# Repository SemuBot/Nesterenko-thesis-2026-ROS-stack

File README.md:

# ROS 2 Stack for Social Humanoid Robot SemuBot

## Project Overview
This repository provides a modular ROS 2 stack architecture for **SemuBot**, an open-source social humanoid robot developed at the University of Tartu.

## Thesis Context
Previous SemuBot thesis works developed separate subsystems (face/neck, audio, speech, vision, power, arms, servo control, and initial ROS 2 integration).  
This repository organizes those efforts into a unified ROS 2 stack with clearer package boundaries and safer integration flow.

## Repository Purpose
The repository is intended to provide a maintainable, buildable, and testable architecture for future students and researchers extending SemuBot.

## Architecture Overview
Main architecture layers:
- robot description
- hardware abstraction
- control
- perception
- interaction/behavior
- navigation
- manipulation
- simulation/visualization
- system monitoring

## Robot Description and Mesh Strategy
- The active `semubot_description` now uses **actual SemuBot visual meshes** for RViz visualization.
- Collision geometry remains **simplified** (cylinders/boxes/spheres) for navigation and simulation stability.
- Nav2 behavior depends primarily on TF, odometry, `/cmd_vel`, `/scan`, and footprint/costmap parameters.
- The decorative visual mesh model is intentionally different from the navigation collision model.

## Package Structure
Primary stack lives in `semubot_ros2_ws/src/`:

- `semubot_description`
- `semubot_bringup`
- `semubot_control`
- `semubot_hardware`
- `semubot_interfaces`
- `semubot_behavior`
- `semubot_audio`
- `semubot_vision`
- `semubot_speech`
- `semubot_face`
- `semubot_arm`
- `semubot_navigation`
- `semubot_moveit_config`
- `semubot_simulation`
- `semubot_system_monitor`
- `semubot_test_tools`

## Requirements
- Ubuntu 24.04 (recommended)
- ROS 2 Jazzy (recommended target)
- Note: some legacy subsystem code was originally developed for ROS 2 Humble. Keep compatibility notes when reusing older components.

## Installation
```bash
cd semubot_ros2_ws
rosdep install --from-paths src --ignore-src -r -y
```

## Build Instructions
```bash
cd semubot_ros2_ws
rosdep install --from-paths src --ignore-src -r -y
colcon build
source install/setup.bash
```

## Launch Instructions
```bash
ros2 launch semubot_bringup visualization.launch.py
ros2 launch semubot_bringup mock_robot.launch.py
ros2 launch semubot_bringup navigation_readiness.launch.py
ros2 launch semubot_bringup demo_behavior.launch.py
```

## Mock Nav2 Integration
Use mock Nav2 mode to validate architecture readiness without controlling the real robot:

```bash
ros2 launch semubot_bringup nav2_mock.launch.py
```

This mode is safe by default and routes `/cmd_vel` through mock/safe nodes only.
See: `semubot_ros2_ws/docs/nav2_mock_integration.md`.

## Basic Testing Commands
```bash
ros2 node list
ros2 topic list
ros2 topic echo /joint_states
ros2 topic echo /odom
ros2 topic echo /semubot/demo_state
ros2 topic pub /cmd_vel geometry_msgs/msg/Twist "{linear: {x: 0.05, y: 0.0, z: 0.0}, angular: {x: 0.0, y: 0.0, z: 0.05}}"
```

## Safe `/cmd_vel` Test
`semubot_hardware/safe_cmd_vel_receiver_node` validates velocity limits and rejects unsafe commands before any real hardware forwarding.

`semubot_hardware/mock_base_hardware_node` is used for navigation readiness: it consumes `/cmd_vel`, publishes mock `/odom`, and broadcasts dynamic `odom -> base_link` TF.

Default safety parameters:
- `max_linear_velocity = 0.10`
- `max_angular_velocity = 0.30`
- `enable_real_motion = false`

## Real Robot Safety Warning
Real robot motion is disabled by default and must only be tested under supervised lab conditions with:
- low velocity limits,
- emergency power access,
- sufficient free space,
- one nearby safety observer.

See full protocol: `semubot_ros2_ws/docs/lab_test_protocol.md`.

## Documentation Links
- Getting started: `semubot_ros2_ws/docs/getting_started.md`
- Architecture: `semubot_ros2_ws/docs/architecture.md`
- Navigation readiness: `semubot_ros2_ws/docs/navigation_readiness.md`
- Testing plan: `semubot_ros2_ws/docs/testing_plan.md`
- Lab safety protocol: `semubot_ros2_ws/docs/lab_test_protocol.md`
- Previous subsystem context: `semubot_ros2_ws/docs/previous_work.md`
- Demos and media index: `semubot_ros2_ws/docs/demos.md`
- Future roadmap: `semubot_ros2_ws/docs/future_work.md`
- Media policy: `semubot_ros2_ws/media/README.md`

## Future Work
Near-term priorities:
- validate real odometry sources and obstacle sensing for Nav2,
- integrate validated hardware drivers behind safety wrappers,
- migrate mock nodes to production subsystem integrations,
- stage Nav2 and MoveIt 2 onboarding,
- expand automated test and CI coverage.

## Contribution Guidelines for Future Students
1. Keep package responsibilities clear and documented.
2. Prefer standard ROS 2 messages unless custom interfaces are necessary.
3. Keep real motion disabled by default in new code paths.
4. Add launch and test instructions with every subsystem change.
5. Place large media in `semubot_ros2_ws/media/` and reference it from `docs/demos.md` (do not overload this root README).

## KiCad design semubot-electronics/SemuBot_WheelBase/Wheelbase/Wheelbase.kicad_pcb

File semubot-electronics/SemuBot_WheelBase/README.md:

# Wheelbase

## Overview

This project implements a BLDC motor control wheelbase using an STM32 microcontroller, 3-phase gate drivers, and high-precision current sensing.

---

## Components

### Microcontroller
* **STM32F303RET6**

### BLDC Driver
* **DRV8353FSRTAR**
  3-phase gate driver for MOSFET control.

### Current Sensing
* **ADS131M03IRUKT**
  3-channel, 24-bit, simultaneous-sampling Delta-Sigma ADC for current measurement.

### MOSFETs
* **AON7262E**
  N-channel MOSFETs for power stage switching.

### Voltage Regulation
* **RT9013-33GB**
  3.3V LDO regulator.

### Power Input & Connectors
* **XT30PW-M**
  Main DC power input connector.

* **MR30PW-M**
  Motor phase power connection.

* **10155435-00011LF (Amphenol)**
  USB Type-C connector.

* **B5B-XH-A_LF__SN_ (JST XH)**
  5-pin connector for peripherals (e.g., Hall/Sensor inputs).

* **DS1013-10SSIB1**
  General purpose I/O connector.

### ESD Protection
* **PRTR5V0U2X**
  ESD protection for data lines.

### Timing & Clock
* **ECS-2520MVLC-081.92-CN-TR**
  8.192 MHz Oscillator.
* **X322516MLB4SI**
  Secondary oscillator for system timing.

### User Interface
* **SWT0211-050010GSA_REVA**
  Tactile switch for system reset or user input.

---

## Technical Summary

### Power Stage
* **MOSFETs:** 18x AON7262E
* **Gate Drivers:** 3x DRV8353FSRTAR
* **Current Sense Resistors:** 9x 10mΩ (2512 package)

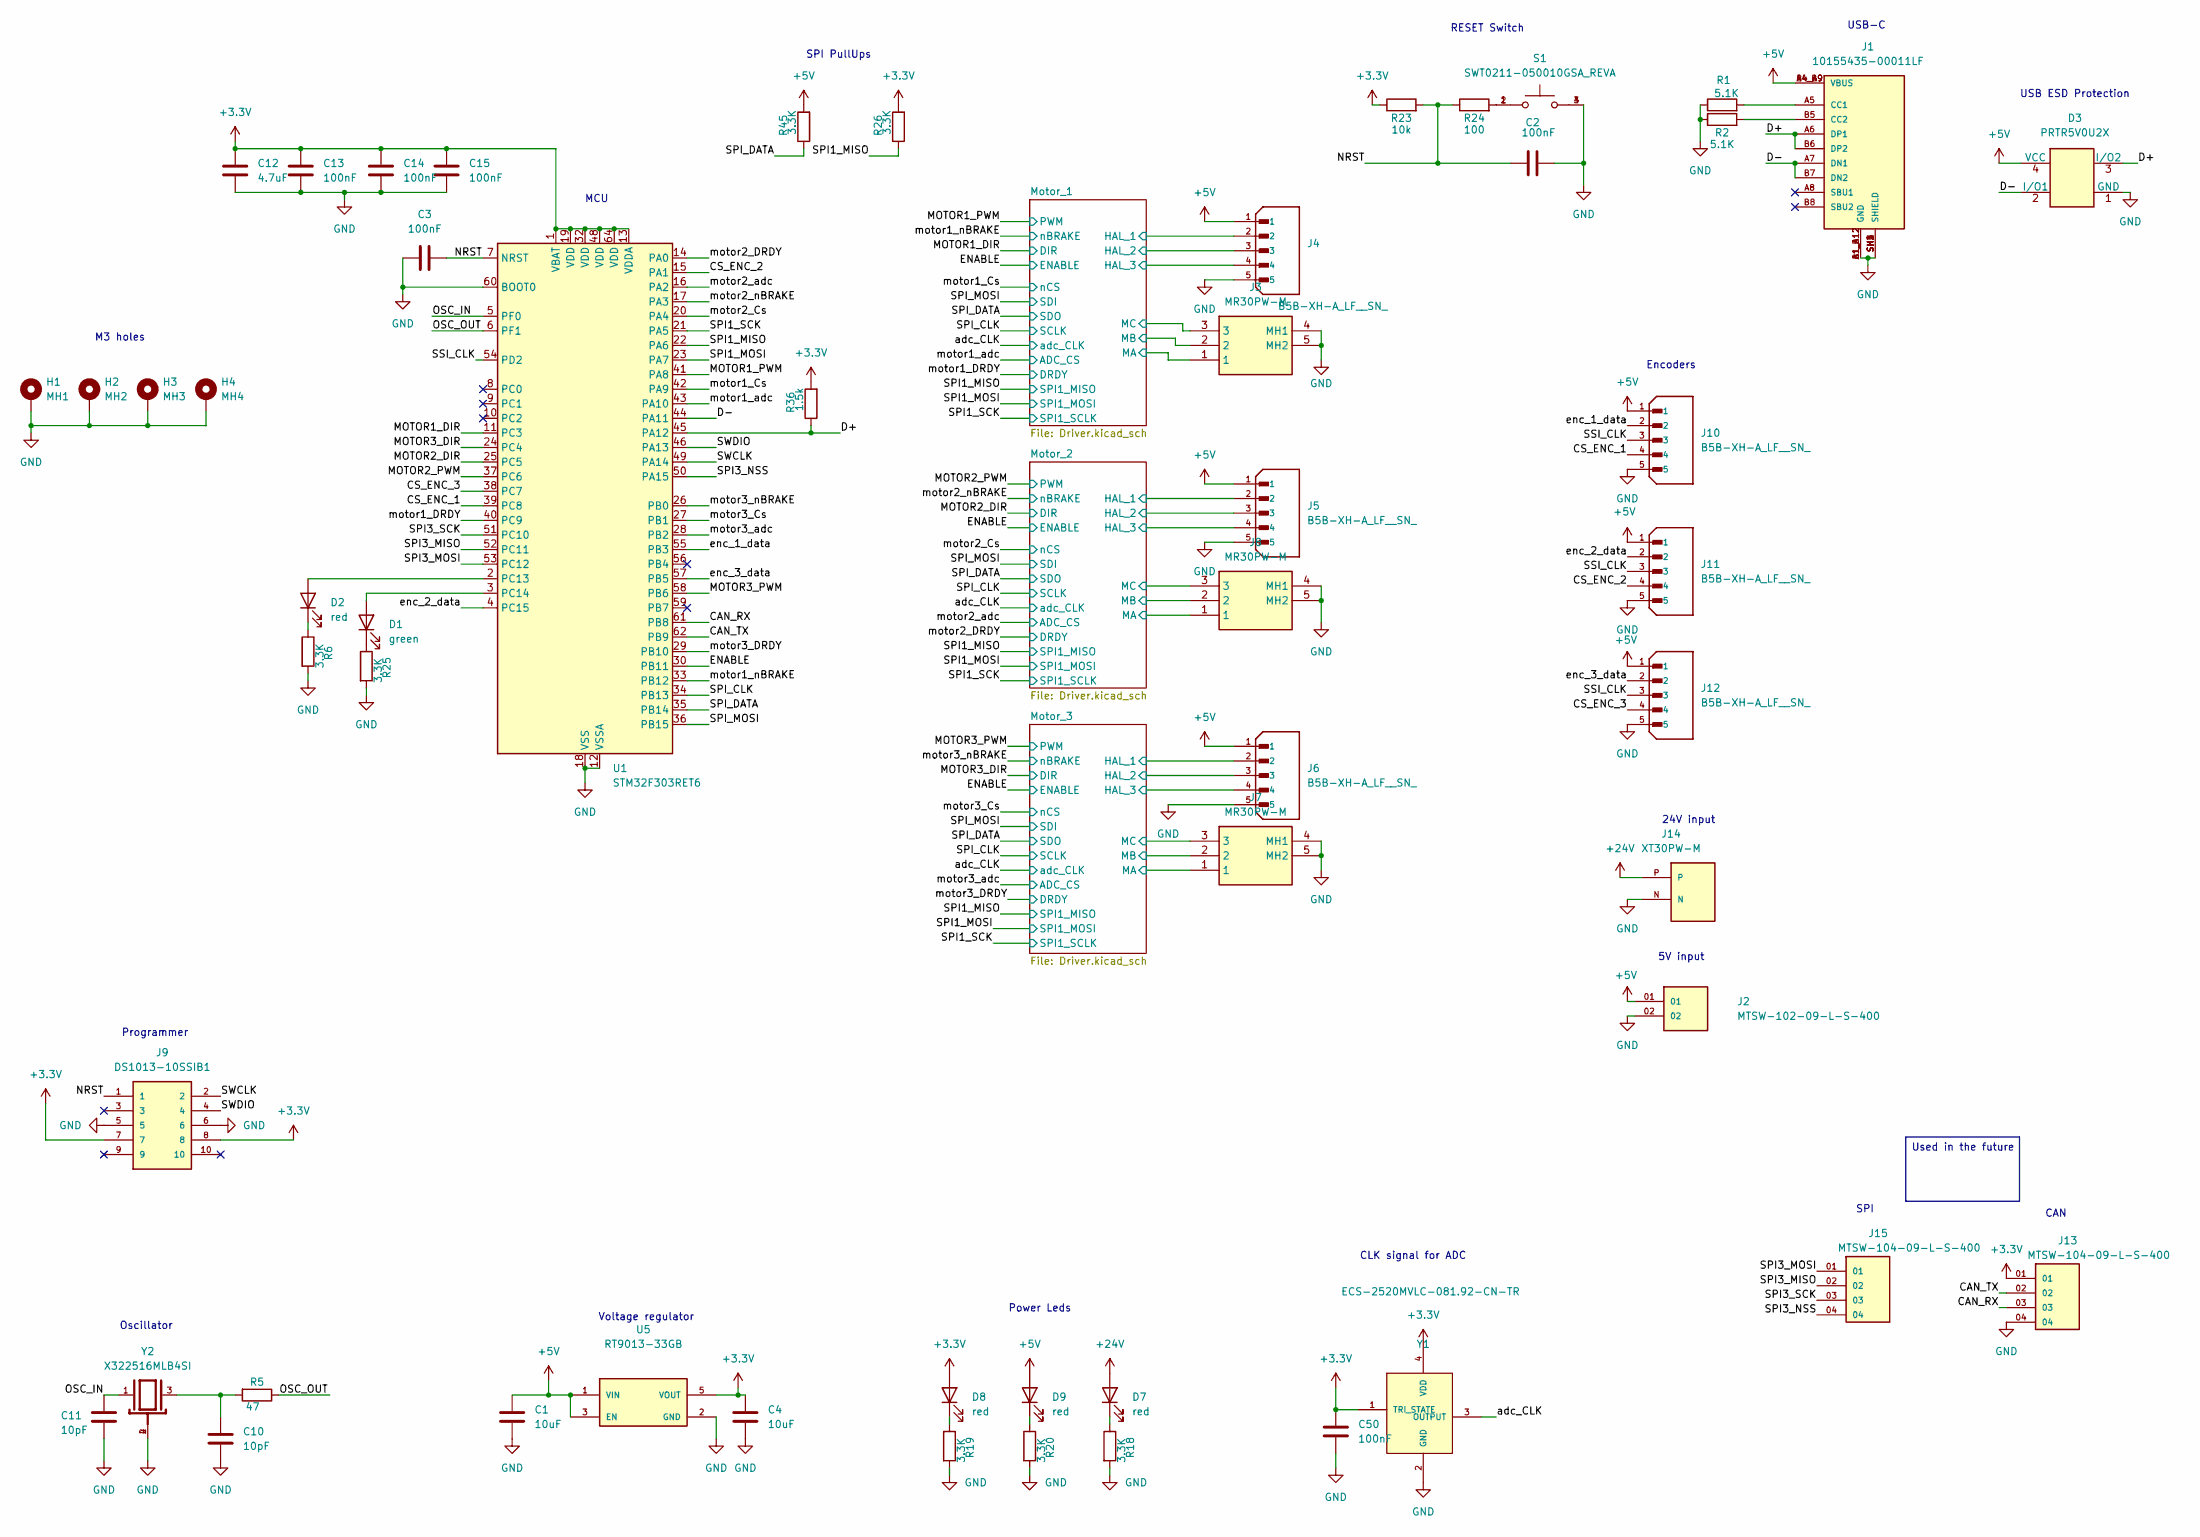
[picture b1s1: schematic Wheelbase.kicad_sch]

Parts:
C1, C4: 10uF; C_0805_2012Metric_Pad1.18x1.45mm_HandSolder
C2, C3, C13, C14, C15, C50: 100nF; C_0603_1608Metric_Pad1.08x0.95mm_HandSolder
C10, C11: 10pF; C_0603_1608Metric_Pad1.08x0.95mm_HandSolder
C12: 4.7uF; C_0603_1608Metric_Pad1.08x0.95mm_HandSolder
D1: green; LED_0603_1608Metric_Pad1.05x0.95mm_HandSolder
D2, D7, D8, D9: red; LED_0603_1608Metric_Pad1.05x0.95mm_HandSolder
D3: PRTR5V0U2X; SOT-143
H1: MH1; MountingHole_3.2mm_M3_Pad_Via
H2: MH2; MountingHole_3.2mm_M3_Pad_Via
H3: MH3; MountingHole_3.2mm_M3_Pad_Via
H4: MH4; MountingHole_3.2mm_M3_Pad_Via
J1: 10155435-00011LF; AMPHENOL_10155435-00011LF; PARTREV C
J2: MTSW-102-09-L-S-400; SAMTEC_MTSW-102-09-L-S-400; PARTREV R
J3, J7, J8: MR30PW-M; MR30PWM; Manufacturer_Part_Number MR30PW-M
J4, J5, J6, J10, J11, J12: B5B-XH-A_LF__SN_; JST_B5B-XH-A_LF__SN_; PARTREV 7/4/21
J9: DS1013-10SSIB1; CONNFLY_DS1013-10SSIB1; PARTREV G
J13, J15: MTSW-104-09-L-S-400; SAMTEC_MTSW-104-09-L-S-400; PARTREV R
J14: XT30PW-M; AMASS_XT30PW-M; PARTREV 1.2
R1, R2: 5.1K; R_0603_1608Metric_Pad0.98x0.95mm_HandSolder
R5: 47; R_0603_1608Metric_Pad0.98x0.95mm_HandSolder
R6, R18, R19, R20, R25, R26, R45: 3.3K; R_0603_1608Metric_Pad0.98x0.95mm_HandSolder
R23: 10k; R_0603_1608Metric_Pad0.98x0.95mm_HandSolder
R24: 100; R_0603_1608Metric_Pad0.98x0.95mm_HandSolder
R36: 1.5k; R_0603_1608Metric_Pad0.98x0.95mm_HandSolder
S1: SWT0211-050010GSA_REVA; SW_SWT0211-050010GSA_REVA; PARTREV A
U1: STM32F303RET6; LQFP-64_10x10mm_P0.5mm
U5: RT9013-33GB; SOT94P279X129-5N; PARTREV Aprill 2011
Y1: ECS-2520MVLC-081.92-CN-TR; OSC_ECS-2520MVLC-081.92-CN-TR; PARTREV 2017
Y2: X322516MLB4SI; OSC_X322516MLB4SI; PARTREV N/A

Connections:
+3.3V: C4.2, C12.1, C13.1, C14.1, C15.1, C50.1, D8.2 (A), J9.7, J9.8, J13.01, R23.1, R26.2, R36.2, U1.1 (VBAT), U1.13 (VDDA), U1.19 (VDD), U1.32 (VDD), U1.48 (VDD), U1.64 (VDD), U5.5 (VOUT), Y1.1 (TRI_STATE), Y1.4 (VDD); also elsewhere on the board
+5V: C1.2, D3.4 (VCC), D9.2 (A), J1.A4_B9 (VBUS), J1.B4_A9 (VBUS), J2.01, J4.1, J5.1, J6.1, J10.1, J11.1, J12.1, R45.2, U5.1 (VIN), U5.3 (EN); also elsewhere on the board
+24V: D7.2 (A), J14.P; also elsewhere on the board
/CAN_RX: J13.03, U1.61 (PB8)
/CAN_TX: J13.02, U1.62 (PB9)
/CS_ENC_1: J10.4, U1.39 (PC8)
/CS_ENC_2: J11.4, U1.15 (PA1)
/CS_ENC_3: J12.4, U1.38 (PC7)
/D+: D3.3 (I/O2), J1.A6 (DP1), J1.B6 (DP2), R36.1, U1.45 (PA12)
/D-: D3.2 (I/O1), J1.A7 (DN1), J1.B7 (DN2), U1.44 (PA11)
/ENABLE: U1.30 (PB11); also elsewhere on the board
/MOTOR1_DIR: U1.11 (PC3); also elsewhere on the board
/MOTOR1_PWM: U1.41 (PA8); also elsewhere on the board
/MOTOR2_DIR: U1.25 (PC5); also elsewhere on the board
/MOTOR2_PWM: U1.37 (PC6); also elsewhere on the board
/MOTOR3_DIR: U1.24 (PC4); also elsewhere on the board
/MOTOR3_PWM: U1.58 (PB6); also elsewhere on the board
/Motor_1/HAL_1: J4.2; also elsewhere on the board
/Motor_1/HAL_2: J4.3; also elsewhere on the board
/Motor_1/HAL_3: J4.4; also elsewhere on the board
/Motor_1/SHA: J3.1; also elsewhere on the board
/Motor_1/SHB: J3.2; also elsewhere on the board
/Motor_1/SHC: J3.3; also elsewhere on the board
/Motor_2/HAL_1: J5.2; also elsewhere on the board
/Motor_2/HAL_2: J5.3; also elsewhere on the board
/Motor_2/HAL_3: J5.4; also elsewhere on the board
/Motor_2/SHA: J8.1; also elsewhere on the board
/Motor_2/SHB: J8.2; also elsewhere on the board
/Motor_2/SHC: J8.3; also elsewhere on the board
/Motor_3/HAL_1: J6.2; also elsewhere on the board
/Motor_3/HAL_2: J6.3; also elsewhere on the board
/Motor_3/HAL_3: J6.4; also elsewhere on the board
/Motor_3/SHA: J7.1; also elsewhere on the board
/Motor_3/SHB: J7.2; also elsewhere on the board
/Motor_3/SHC: J7.3; also elsewhere on the board
/NRST: C2.2, C3.2, J9.1, R23.2, R24.1, U1.7 (NRST)
/OSC_IN: C11.1, U1.5 (PF0), Y2.1
/OSC_OUT: R5.1, U1.6 (PF1)
/SPI1_MISO: R26.1, U1.22 (PA6); also elsewhere on the board
/SPI1_MOSI: U1.23 (PA7); also elsewhere on the board
/SPI1_SCK: U1.21 (PA5); also elsewhere on the board
/SPI3_MISO: J15.02, U1.52 (PC11)
/SPI3_MOSI: J15.01, U1.53 (PC12)
/SPI3_NSS: J15.04, U1.50 (PA15)
/SPI3_SCK: J15.03, U1.51 (PC10)
/SPI_CLK: U1.34 (PB13); also elsewhere on the board
/SPI_DATA: R45.1, U1.35 (PB14); also elsewhere on the board
/SPI_MOSI: U1.36 (PB15); also elsewhere on the board
/SSI_CLK: J10.3, J11.3, J12.3, U1.54 (PD2)
/SWCLK: J9.2, U1.49 (PA14)
/SWDIO: J9.4, U1.46 (PA13)
/adc_CLK: Y1.3 (OUTPUT); also elsewhere on the board
/enc_1_data: J10.2, U1.55 (PB3)
/enc_2_data: J11.2, U1.4 (PC15)
/enc_3_data: J12.2, U1.57 (PB5)
/motor1_Cs: U1.42 (PA9); also elsewhere on the board
/motor1_DRDY: U1.40 (PC9); also elsewhere on the board
/motor1_adc: U1.43 (PA10); also elsewhere on the board
/motor1_nBRAKE: U1.33 (PB12); also elsewhere on the board
/motor2_Cs: U1.20 (PA4); also elsewhere on the board
/motor2_DRDY: U1.14 (PA0); also elsewhere on the board
/motor2_adc: U1.16 (PA2); also elsewhere on the board
/motor2_nBRAKE: U1.17 (PA3); also elsewhere on the board
/motor3_Cs: U1.27 (PB1); also elsewhere on the board
/motor3_DRDY: U1.29 (PB10); also elsewhere on the board
/motor3_adc: U1.28 (PB2); also elsewhere on the board
/motor3_nBRAKE: U1.26 (PB0); also elsewhere on the board
GND: C1.1, C2.1, C3.1, C4.1, C10.1, C11.2, C12.2, C13.2, C14.2, C15.2, C50.2, D3.1 (GND), H1.1, H2.1, H3.1, H4.1, J1.A1_B12 (GND), J1.B1_A12 (GND), J1.SH1 (SHIELD), J1.SH2 (SHIELD), J1.SH3 (SHIELD), J1.SH4 (SHIELD), J2.02, J3.4 (MH1), J3.5 (MH2), J4.5, J5.5, J6.5, J7.4 (MH1), J7.5 (MH2), J8.4 (MH1), J8.5 (MH2), J9.5, J9.6, J10.5, J11.5, J12.5, J13.04, J14.N, R1.1, R2.1, R6.2, R18.2, R19.2, R20.2, R25.2, S1.3, S1.4, U1.12 (VSSA), U1.18 (VSS), U1.31 (VSS), U1.47 (VSS), U1.60 (BOOT0), U1.63 (VSS), U5.2 (GND), Y1.2 (GND), Y2.2, Y2.4; also elsewhere on the board
unnamed: C10.2, R5.2, Y2.3
unnamed: D1.2 (A), U1.3 (PC14)
unnamed: D1.1 (K), R25.1
unnamed: D2.2 (A), U1.2 (PC13)
unnamed: D2.1 (K), R6.1
unnamed: D7.1 (K), R18.1
unnamed: D8.1 (K), R19.1
unnamed: D9.1 (K), R20.1
unnamed: J1.A5 (CC1), R1.2
unnamed: J1.B5 (CC2), R2.2
unnamed: R24.2, S1.1, S1.2

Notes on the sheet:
24V input
Encoders
SPI
MCU
M3 holes
RESET Switch
Oscillator
USB-C
USB ESD Protection
CAN
SPI PullUps
Power Leds
Programmer
CLK signal for ADC
Voltage regulator
5V input
Used in the future

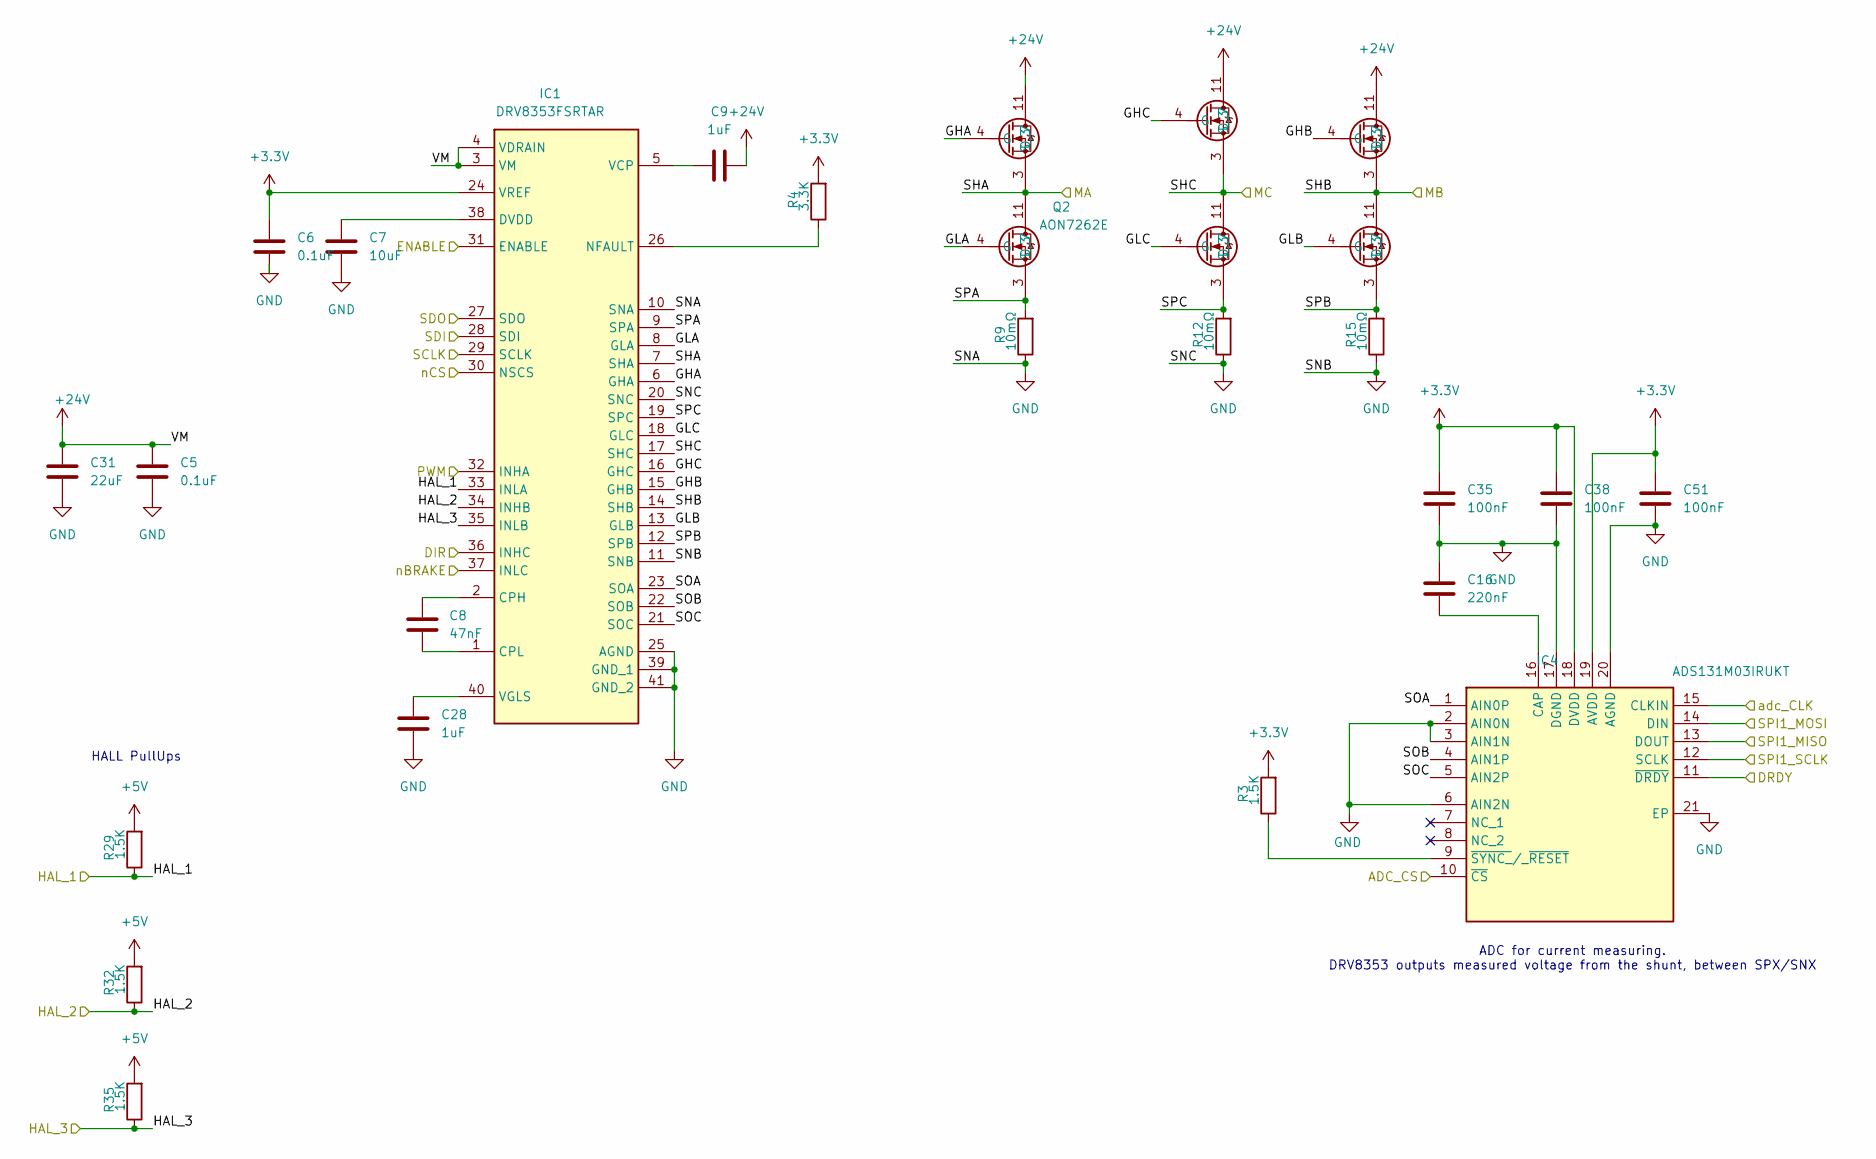
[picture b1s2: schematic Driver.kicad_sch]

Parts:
C5, C6: 0.1uF; C_0603_1608Metric_Pad1.08x0.95mm_HandSolder
C7: 10uF; C_0603_1608Metric_Pad1.08x0.95mm_HandSolder
C8: 47nF; C_0603_1608Metric_Pad1.08x0.95mm_HandSolder
C9, C28: 1uF; C_0603_1608Metric_Pad1.08x0.95mm_HandSolder
C16: 220nF; C_0603_1608Metric_Pad1.08x0.95mm_HandSolder
C31: 22uF; C_0805_2012Metric_Pad1.18x1.45mm_HandSolder
C35, C38, C51: 100nF; C_0603_1608Metric_Pad1.08x0.95mm_HandSolder
IC1: DRV8353FSRTAR; QFN50P600X600X80-41N-D; Mouser Part Number 595-DRV8353FSRTAR
IC4: ADS131M03IRUKT; QFN40P300X300X80-21N-D; Manufacturer_Part_Number ADS131M03IRUKT
Q1, Q2, Q3, Q5, Q6, Q19: AON7262E; Manufacturer_Part_Number AON7262E
R3, R29, R32, R35: 1.5K; R_0603_1608Metric_Pad0.98x0.95mm_HandSolder
R4: 3.3K; R_0603_1608Metric_Pad0.98x0.95mm_HandSolder
R9, R12, R15: 10mΩ; R_2512_6332Metric_Pad1.40x3.35mm_HandSolder

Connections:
+3.3V: C6.1, C35.1, C38.1, C51.1, IC1.24 (VREF), IC4.18 (DVDD), IC4.19 (AVDD), R3.2, R4.2; also elsewhere on the board
+5V: R29.2, R32.2, R35.2; also elsewhere on the board
+24V: C5.1, C9.2, C31.2, IC1.3 (VM), IC1.4 (VDRAIN), Q1.5 (D_1), Q1.6 (D_2), Q1.7 (D_3), Q1.8 (D_4), Q1.9 (D_5), Q1.10 (D_6), Q1.11 (D_7), Q3.5 (D_1), Q3.6 (D_2), Q3.7 (D_3), Q3.8 (D_4), Q3.9 (D_5), Q3.10 (D_6), Q3.11 (D_7), Q5.5 (D_1), Q5.6 (D_2), Q5.7 (D_3), Q5.8 (D_4), Q5.9 (D_5), Q5.10 (D_6), Q5.11 (D_7); also elsewhere on the board
/ENABLE: IC1.31 (ENABLE); also elsewhere on the board
/MOTOR1_DIR: IC1.36 (INHC); also elsewhere on the board
/MOTOR1_PWM: IC1.32 (INHA); also elsewhere on the board
/Motor_1/GHA: IC1.6 (GHA), Q1.4 (G)
/Motor_1/GHB: IC1.15 (GHB), Q3.4 (G)
/Motor_1/GHC: IC1.16 (GHC), Q5.4 (G)
/Motor_1/GLA: IC1.8 (GLA), Q2.4 (G)
/Motor_1/GLB: IC1.13 (GLB), Q19.4 (G)
/Motor_1/GLC: IC1.18 (GLC), Q6.4 (G)
/Motor_1/HAL_1: IC1.33 (INLA), R29.1; also elsewhere on the board
/Motor_1/HAL_2: IC1.34 (INHB), R32.1; also elsewhere on the board
/Motor_1/HAL_3: IC1.35 (INLB), R35.1; also elsewhere on the board
/Motor_1/SHA: IC1.7 (SHA), Q1.1 (S_1), Q1.2 (S_2), Q1.3 (S_3), Q2.5 (D_1), Q2.6 (D_2), Q2.7 (D_3), Q2.8 (D_4), Q2.9 (D_5), Q2.10 (D_6), Q2.11 (D_7); also elsewhere on the board
/Motor_1/SHB: IC1.14 (SHB), Q3.1 (S_1), Q3.2 (S_2), Q3.3 (S_3), Q19.5 (D_1), Q19.6 (D_2), Q19.7 (D_3), Q19.8 (D_4), Q19.9 (D_5), Q19.10 (D_6), Q19.11 (D_7); also elsewhere on the board
/Motor_1/SHC: IC1.17 (SHC), Q5.1 (S_1), Q5.2 (S_2), Q5.3 (S_3), Q6.5 (D_1), Q6.6 (D_2), Q6.7 (D_3), Q6.8 (D_4), Q6.9 (D_5), Q6.10 (D_6), Q6.11 (D_7); also elsewhere on the board
/Motor_1/SOA: IC1.23 (SOA), IC4.1 (AIN0P)
/Motor_1/SOB: IC1.22 (SOB), IC4.4 (AIN1P)
/Motor_1/SOC: IC1.21 (SOC), IC4.5 (AIN2P)
/Motor_1/SPA: IC1.9 (SPA), Q2.1 (S_1), Q2.2 (S_2), Q2.3 (S_3), R9.2
/Motor_1/SPB: IC1.12 (SPB), Q19.1 (S_1), Q19.2 (S_2), Q19.3 (S_3), R15.2
/Motor_1/SPC: IC1.19 (SPC), Q6.1 (S_1), Q6.2 (S_2), Q6.3 (S_3), R12.2
/SPI1_MISO: IC4.13 (DOUT); also elsewhere on the board
/SPI1_MOSI: IC4.14 (DIN); also elsewhere on the board
/SPI1_SCK: IC4.12 (SCLK); also elsewhere on the board
/SPI_CLK: IC1.29 (SCLK); also elsewhere on the board
/SPI_DATA: IC1.27 (SDO); also elsewhere on the board
/SPI_MOSI: IC1.28 (SDI); also elsewhere on the board
/adc_CLK: IC4.15 (CLKIN); also elsewhere on the board
/motor1_Cs: IC1.30 (NSCS); also elsewhere on the board
/motor1_DRDY: IC4.11 (~DRDY); also elsewhere on the board
/motor1_adc: IC4.10 (~CS); also elsewhere on the board
/motor1_nBRAKE: IC1.37 (INLC); also elsewhere on the board
GND: C5.2, C6.2, C7.2, C16.1, C28.1, C31.1, C35.2, C38.2, C51.2, IC1.10 (SNA), IC1.11 (SNB), IC1.20 (SNC), IC1.25 (AGND), IC1.39 (GND_1), IC1.41 (GND_2), IC4.2 (AIN0N), IC4.3 (AIN1N), IC4.6 (AIN2N), IC4.17 (DGND), IC4.20 (AGND), IC4.21 (EP), R9.1, R12.1, R15.1; also elsewhere on the board
unnamed: C8.1, IC1.2 (CPH)
unnamed: C8.2, IC1.1 (CPL)
unnamed: C7.1, IC1.38 (DVDD)
unnamed: IC1.26 (NFAULT), R4.1
unnamed: C9.1, IC1.5 (VCP)
unnamed: C28.2, IC1.40 (VGLS)
unnamed: C16.2, IC4.16 (CAP)
unnamed: IC4.9 (~SYNC_/_~RESET), R3.1

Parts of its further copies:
C17, C18, C23, C24: 0.1uF; C_0603_1608Metric_Pad1.08x0.95mm_HandSolder
C19, C25: 10uF; C_0603_1608Metric_Pad1.08x0.95mm_HandSolder
C20, C26: 47nF; C_0603_1608Metric_Pad1.08x0.95mm_HandSolder
C21, C27, C29, C30: 1uF; C_0603_1608Metric_Pad1.08x0.95mm_HandSolder
C22, C34: 220nF; C_0603_1608Metric_Pad1.08x0.95mm_HandSolder
C32, C33: 22uF; C_0805_2012Metric_Pad1.18x1.45mm_HandSolder
C36, C37, C39, C40, C52, C53: 100nF; C_0603_1608Metric_Pad1.08x0.95mm_HandSolder
IC2, IC3: DRV8353FSRTAR; QFN50P600X600X80-41N-D; Mouser Part Number 595-DRV8353FSRTAR
IC5, IC6: ADS131M03IRUKT; QFN40P300X300X80-21N-D; Manufacturer_Part_Number ADS131M03IRUKT
Q4, Q7, Q8, Q9, Q10, Q11, Q12, Q13, Q14, Q15, Q20, Q21: AON7262E; Manufacturer_Part_Number AON7262E
R7, R8: 3.3K; R_0603_1608Metric_Pad0.98x0.95mm_HandSolder
R10, R11, R13, R14, R16, R17: 10mΩ; R_2512_6332Metric_Pad1.40x3.35mm_HandSolder
R21, R22, R30, R31, R33, R34, R37, R38: 1.5K; R_0603_1608Metric_Pad0.98x0.95mm_HandSolder

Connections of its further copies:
+3.3V: C18.1, C24.1, C36.1, C37.1, C39.1, C40.1, C52.1, C53.1, IC2.24 (VREF), IC3.24 (VREF), IC5.18 (DVDD), IC5.19 (AVDD), IC6.18 (DVDD), IC6.19 (AVDD), R7.2, R8.2, R21.2, R22.2; also elsewhere on the board
+5V: R30.2, R31.2, R33.2, R34.2, R37.2, R38.2; also elsewhere on the board
+24V: C17.1, C21.2, C23.1, C27.2, C32.2, C33.2, IC2.3 (VM), IC2.4 (VDRAIN), IC3.3 (VM), IC3.4 (VDRAIN), Q4.5 (D_1), Q4.6 (D_2), Q4.7 (D_3), Q4.8 (D_4), Q4.9 (D_5), Q4.10 (D_6), Q4.11 (D_7), Q7.5 (D_1), Q7.6 (D_2), Q7.7 (D_3), Q7.8 (D_4), Q7.9 (D_5), Q7.10 (D_6), Q7.11 (D_7), Q9.5 (D_1), Q9.6 (D_2), Q9.7 (D_3), Q9.8 (D_4), Q9.9 (D_5), Q9.10 (D_6), Q9.11 (D_7), Q11.5 (D_1), Q11.6 (D_2), Q11.7 (D_3), Q11.8 (D_4), Q11.9 (D_5), Q11.10 (D_6), Q11.11 (D_7), Q13.5 (D_1), Q13.6 (D_2), Q13.7 (D_3), Q13.8 (D_4), Q13.9 (D_5), Q13.10 (D_6), Q13.11 (D_7), Q15.5 (D_1), Q15.6 (D_2), Q15.7 (D_3), Q15.8 (D_4), Q15.9 (D_5), Q15.10 (D_6), Q15.11 (D_7); also elsewhere on the board
/ENABLE: IC2.31 (ENABLE), IC3.31 (ENABLE); also elsewhere on the board
/MOTOR2_DIR: IC2.36 (INHC); also elsewhere on the board
/MOTOR2_PWM: IC2.32 (INHA); also elsewhere on the board
/MOTOR3_DIR: IC3.36 (INHC); also elsewhere on the board
/MOTOR3_PWM: IC3.32 (INHA); also elsewhere on the board
/Motor_2/GHA: IC2.6 (GHA), Q7.4 (G)
/Motor_2/GHB: IC2.15 (GHB), Q4.4 (G)
/Motor_2/GHC: IC2.16 (GHC), Q11.4 (G)
/Motor_2/GLA: IC2.8 (GLA), Q8.4 (G)
/Motor_2/GLB: IC2.13 (GLB), Q20.4 (G)
/Motor_2/GLC: IC2.18 (GLC), Q10.4 (G)
/Motor_2/HAL_1: IC2.33 (INLA), R30.1; also elsewhere on the board
/Motor_2/HAL_2: IC2.34 (INHB), R33.1; also elsewhere on the board
/Motor_2/HAL_3: IC2.35 (INLB), R37.1; also elsewhere on the board
/Motor_2/SHA: IC2.7 (SHA), Q7.1 (S_1), Q7.2 (S_2), Q7.3 (S_3), Q8.5 (D_1), Q8.6 (D_2), Q8.7 (D_3), Q8.8 (D_4), Q8.9 (D_5), Q8.10 (D_6), Q8.11 (D_7); also elsewhere on the board
/Motor_2/SHB: IC2.14 (SHB), Q4.1 (S_1), Q4.2 (S_2), Q4.3 (S_3), Q20.5 (D_1), Q20.6 (D_2), Q20.7 (D_3), Q20.8 (D_4), Q20.9 (D_5), Q20.10 (D_6), Q20.11 (D_7); also elsewhere on the board
/Motor_2/SHC: IC2.17 (SHC), Q10.5 (D_1), Q10.6 (D_2), Q10.7 (D_3), Q10.8 (D_4), Q10.9 (D_5), Q10.10 (D_6), Q10.11 (D_7), Q11.1 (S_1), Q11.2 (S_2), Q11.3 (S_3); also elsewhere on the board
/Motor_2/SOA: IC2.23 (SOA), IC5.1 (AIN0P)
/Motor_2/SOB: IC2.22 (SOB), IC5.4 (AIN1P)
/Motor_2/SOC: IC2.21 (SOC), IC5.5 (AIN2P)
/Motor_2/SPA: IC2.9 (SPA), Q8.1 (S_1), Q8.2 (S_2), Q8.3 (S_3), R10.2
/Motor_2/SPB: IC2.12 (SPB), Q20.1 (S_1), Q20.2 (S_2), Q20.3 (S_3), R16.2
/Motor_2/SPC: IC2.19 (SPC), Q10.1 (S_1), Q10.2 (S_2), Q10.3 (S_3), R13.2
/Motor_3/GHA: IC3.6 (GHA), Q13.4 (G)
/Motor_3/GHB: IC3.15 (GHB), Q9.4 (G)
/Motor_3/GHC: IC3.16 (GHC), Q15.4 (G)
/Motor_3/GLA: IC3.8 (GLA), Q14.4 (G)
/Motor_3/GLB: IC3.13 (GLB), Q21.4 (G)
/Motor_3/GLC: IC3.18 (GLC), Q12.4 (G)
/Motor_3/HAL_1: IC3.33 (INLA), R31.1; also elsewhere on the board
/Motor_3/HAL_2: IC3.34 (INHB), R34.1; also elsewhere on the board
/Motor_3/HAL_3: IC3.35 (INLB), R38.1; also elsewhere on the board
/Motor_3/SHA: IC3.7 (SHA), Q13.1 (S_1), Q13.2 (S_2), Q13.3 (S_3), Q14.5 (D_1), Q14.6 (D_2), Q14.7 (D_3), Q14.8 (D_4), Q14.9 (D_5), Q14.10 (D_6), Q14.11 (D_7); also elsewhere on the board
/Motor_3/SHB: IC3.14 (SHB), Q9.1 (S_1), Q9.2 (S_2), Q9.3 (S_3), Q21.5 (D_1), Q21.6 (D_2), Q21.7 (D_3), Q21.8 (D_4), Q21.9 (D_5), Q21.10 (D_6), Q21.11 (D_7); also elsewhere on the board
/Motor_3/SHC: IC3.17 (SHC), Q12.5 (D_1), Q12.6 (D_2), Q12.7 (D_3), Q12.8 (D_4), Q12.9 (D_5), Q12.10 (D_6), Q12.11 (D_7), Q15.1 (S_1), Q15.2 (S_2), Q15.3 (S_3); also elsewhere on the board
/Motor_3/SOA: IC3.23 (SOA), IC6.1 (AIN0P)
/Motor_3/SOB: IC3.22 (SOB), IC6.4 (AIN1P)
/Motor_3/SOC: IC3.21 (SOC), IC6.5 (AIN2P)
/Motor_3/SPA: IC3.9 (SPA), Q14.1 (S_1), Q14.2 (S_2), Q14.3 (S_3), R11.2
/Motor_3/SPB: IC3.12 (SPB), Q21.1 (S_1), Q21.2 (S_2), Q21.3 (S_3), R17.2
/Motor_3/SPC: IC3.19 (SPC), Q12.1 (S_1), Q12.2 (S_2), Q12.3 (S_3), R14.2
/SPI1_MISO: IC5.13 (DOUT), IC6.13 (DOUT); also elsewhere on the board
/SPI1_MOSI: IC5.14 (DIN), IC6.14 (DIN); also elsewhere on the board
/SPI1_SCK: IC5.12 (SCLK), IC6.12 (SCLK); also elsewhere on the board
/SPI_CLK: IC2.29 (SCLK), IC3.29 (SCLK); also elsewhere on the board
/SPI_DATA: IC2.27 (SDO), IC3.27 (SDO); also elsewhere on the board
/SPI_MOSI: IC2.28 (SDI), IC3.28 (SDI); also elsewhere on the board
/adc_CLK: IC5.15 (CLKIN), IC6.15 (CLKIN); also elsewhere on the board
/motor2_Cs: IC2.30 (NSCS); also elsewhere on the board
/motor2_DRDY: IC5.11 (~DRDY); also elsewhere on the board
/motor2_adc: IC5.10 (~CS); also elsewhere on the board
/motor2_nBRAKE: IC2.37 (INLC); also elsewhere on the board
/motor3_Cs: IC3.30 (NSCS); also elsewhere on the board
/motor3_DRDY: IC6.11 (~DRDY); also elsewhere on the board
/motor3_adc: IC6.10 (~CS); also elsewhere on the board
/motor3_nBRAKE: IC3.37 (INLC); also elsewhere on the board
GND: C17.2, C18.2, C19.2, C22.1, C23.2, C24.2, C25.2, C29.1, C30.1, C32.1, C33.1, C34.1, C36.2, C37.2, C39.2, C40.2, C52.2, C53.2, IC2.10 (SNA), IC2.11 (SNB), IC2.20 (SNC), IC2.25 (AGND), IC2.39 (GND_1), IC2.41 (GND_2), IC3.10 (SNA), IC3.11 (SNB), IC3.20 (SNC), IC3.25 (AGND), IC3.39 (GND_1), IC3.41 (GND_2), IC5.2 (AIN0N), IC5.3 (AIN1N), IC5.6 (AIN2N), IC5.17 (DGND), IC5.20 (AGND), IC5.21 (EP), IC6.2 (AIN0N), IC6.3 (AIN1N), IC6.6 (AIN2N), IC6.17 (DGND), IC6.20 (AGND), IC6.21 (EP), R10.1, R11.1, R13.1, R14.1, R16.1, R17.1; also elsewhere on the board
unnamed: C20.1, IC2.2 (CPH)
unnamed: C20.2, IC2.1 (CPL)
unnamed: C19.1, IC2.38 (DVDD)
unnamed: IC2.26 (NFAULT), R7.1
unnamed: C21.1, IC2.5 (VCP)
unnamed: C29.2, IC2.40 (VGLS)
unnamed: C26.1, IC3.2 (CPH)
unnamed: C26.2, IC3.1 (CPL)
unnamed: C25.1, IC3.38 (DVDD)
unnamed: IC3.26 (NFAULT), R8.1
unnamed: C27.1, IC3.5 (VCP)
unnamed: C30.2, IC3.40 (VGLS)
unnamed: C22.2, IC5.16 (CAP)
unnamed: IC5.9 (~SYNC_/_~RESET), R21.1
unnamed: C34.2, IC6.16 (CAP)
unnamed: IC6.9 (~SYNC_/_~RESET), R22.1

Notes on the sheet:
HALL PullUps
ADC for current measuring. DRV8353 outputs measured voltage from the shunt, between SPX/SNX

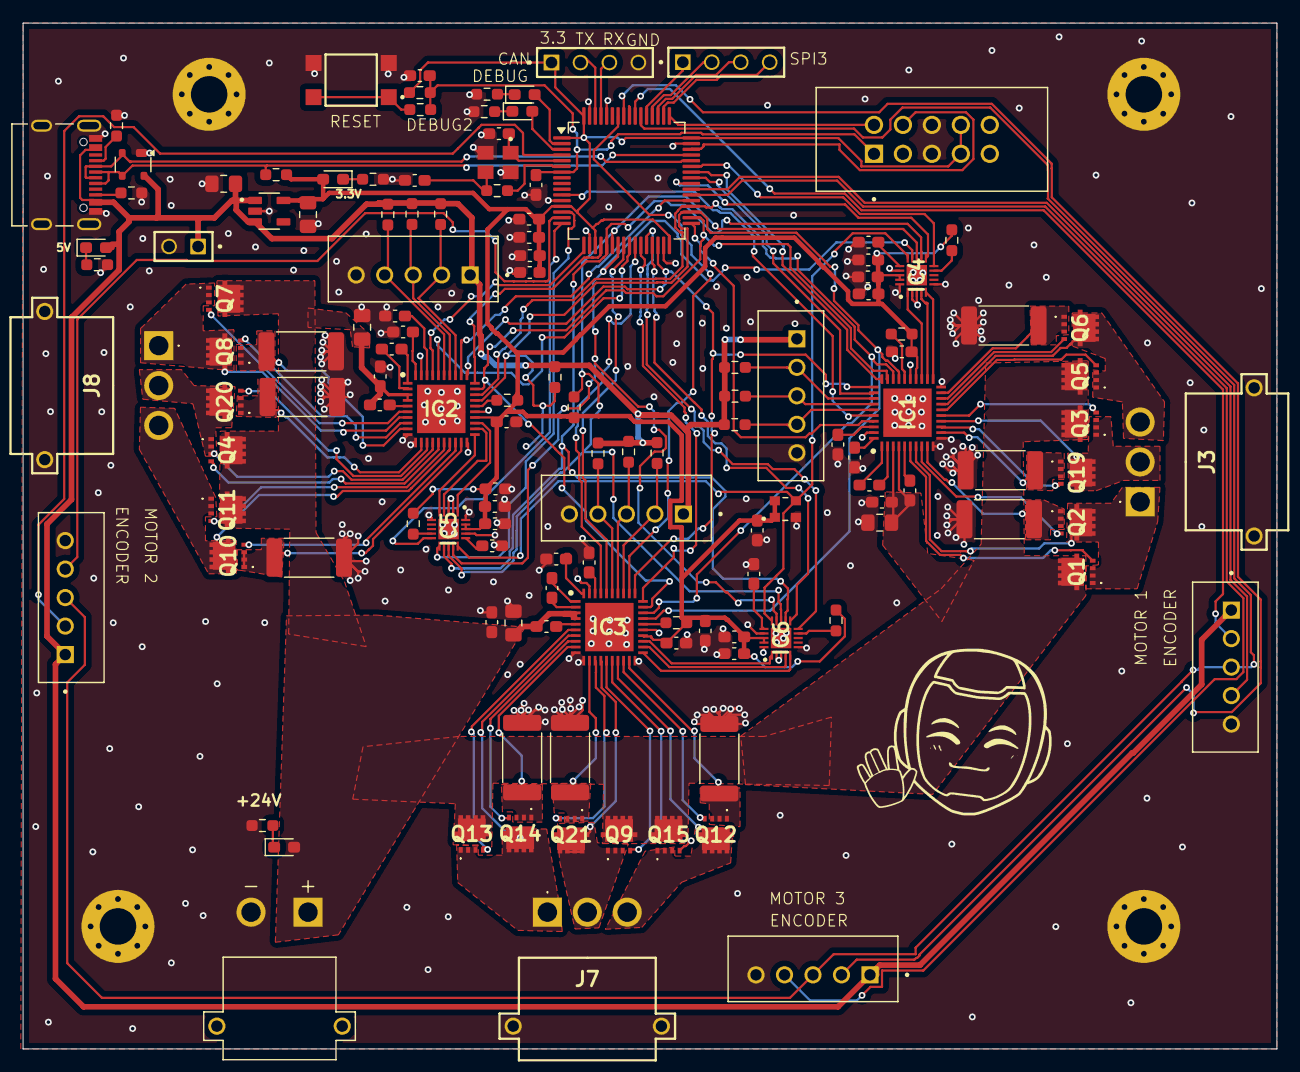
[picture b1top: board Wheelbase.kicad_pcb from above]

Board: 2 copper layers, 110.0 x 90.0 mm, 135 parts (0 on the bottom side), 139 nets.

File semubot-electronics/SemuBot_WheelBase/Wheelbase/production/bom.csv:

Designator,Footprint,Quantity,Value,LCSC Part #
"C1, C4",0805,2,10uF,
"C10, C11",0603,2,10pF,
C12,0603,1,4.7uF,
"C13, C14, C15, C2, C3, C35, C36, C37, C38, C39, C40, C50, C51, C52, C53",0603,15,100nF,
"C16, C22, C34",0603,3,220nF,
"C17, C18, C23, C24, C5, C6",0603,6,0.1uF,
"C19, C25, C7",0603,3,10uF,
"C20, C26, C8",0603,3,47nF,
"C21, C27, C28, C29, C30, C9",0603,6,1uF,
"C31, C32, C33",0805,3,22uF,
D1,0603,1,green,
"D2, D7, D8, D9",0603,4,red,
D3,SOT-143,1,PRTR5V0U2X,
"IC1, IC2, IC3",QFN50P600X600X80-41N-D,3,DRV8353FSRTAR,
"IC4, IC5, IC6",QFN40P300X300X80-21N-D,3,ADS131M03IRUKT,
J1,AMPHENOL_10155435-00011LF,1,10155435-00011LF,
"J10, J11, J12, J4, J5, J6",JST_B5B-XH-A_LF__SN_,6,B5B-XH-A_LF__SN_,
"J13, J15",SAMTEC_MTSW-104-09-L-S-400,2,MTSW-104-09-L-S-400,
J14,AMASS_XT30PW-M,1,XT30PW-M,
J2,SAMTEC_MTSW-102-09-L-S-400,1,MTSW-102-09-L-S-400,
"J3, J7, J8",MR30PWM,3,MR30PW-M,
J9,CONNFLY_DS1013-10SSIB1,1,DS1013-10SSIB1,
"Q1, Q10, Q11, Q12, Q13, Q14, Q15, Q19, Q2, Q20, Q21, Q3, Q4, Q5, Q6, Q7, Q8, Q9",AON7262E,18,AON7262E,
"R1, R2",0603,2,5.1K,
"R10, R11, R12, R13, R14, R15, R16, R17, R9",2512,9,10mΩ,
"R18, R19, R20, R25, R26, R4, R45, R6, R7, R8",0603,10,3.3K,
"R21, R22, R29, R3, R30, R31, R32, R33, R34, R35, R36, R37, R38",0603,13,1.5K,
R23,0603,1,10k,
R24,0603,1,100,
R5,0603,1,47,
S1,SW_SWT0211-050010GSA_REVA,1,SWT0211-050010GSA_REVA,
U1,LQFP-64_10x10mm_P0.5mm,1,STM32F303RET6,
U5,SOT94P279X129-5N,1,RT9013-33GB,
Y1,OSC_ECS-2520MVLC-081.92-CN-TR,1,ECS-2520MVLC-081.92-CN-TR,
Y2,OSC_X322516MLB4SI,1,X322516MLB4SI,

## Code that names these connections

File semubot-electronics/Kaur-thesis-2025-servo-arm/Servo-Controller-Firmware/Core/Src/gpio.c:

/* USER CODE BEGIN Header */
/**
  ******************************************************************************
  * @file    gpio.c
  * @brief   This file provides code for the configuration
  *          of all used GPIO pins.
  ******************************************************************************
  * @attention
  *
  * Copyright (c) 2025 STMicroelectronics.
  * All rights reserved.
  *
  * This software is licensed under terms that can be found in the LICENSE file
  * in the root directory of this software component.
  * If no LICENSE file comes with this software, it is provided AS-IS.
  *
  ******************************************************************************
  */
/* USER CODE END Header */

/* Includes ------------------------------------------------------------------*/
#include "gpio.h"

/* USER CODE BEGIN 0 */

/* USER CODE END 0 */

/*----------------------------------------------------------------------------*/
/* Configure GPIO                                                             */
/*----------------------------------------------------------------------------*/
/* USER CODE BEGIN 1 */

/* USER CODE END 1 */

/** Configure pins as
        * Analog
        * Input
        * Output
        * EVENT_OUT
        * EXTI
        * Free pins are configured automatically as Analog (this feature is enabled through
        * the Code Generation settings)
*/
void MX_GPIO_Init(void)
{

  GPIO_InitTypeDef GPIO_InitStruct = {0};

  /* GPIO Ports Clock Enable */
  __HAL_RCC_GPIOC_CLK_ENABLE();
  __HAL_RCC_GPIOF_CLK_ENABLE();
  __HAL_RCC_GPIOA_CLK_ENABLE();
  __HAL_RCC_GPIOB_CLK_ENABLE();
  __HAL_RCC_GPIOD_CLK_ENABLE();

  /*Configure GPIO pin Output Level */
  HAL_GPIO_WritePin(GPIOC, GPIO_PIN_13|GPIO_PIN_14|GPIO_PIN_15|GPIO_PIN_8
                          |GPIO_PIN_9|GPIO_PIN_10|GPIO_PIN_11|GPIO_PIN_12, GPIO_PIN_RESET);

  /*Configure GPIO pins : PC13 PC14 PC15 PC8
                           PC9 PC10 PC11 PC12 */
  GPIO_InitStruct.Pin = GPIO_PIN_13|GPIO_PIN_14|GPIO_PIN_15|GPIO_PIN_8
                          |GPIO_PIN_9|GPIO_PIN_10|GPIO_PIN_11|GPIO_PIN_12;
  GPIO_InitStruct.Mode = GPIO_MODE_OUTPUT_PP;
  GPIO_InitStruct.Pull = GPIO_NOPULL;
  GPIO_InitStruct.Speed = GPIO_SPEED_FREQ_LOW;
  HAL_GPIO_Init(GPIOC, &GPIO_InitStruct);

  /*Configure GPIO pins : PF0 PF1 */
  GPIO_InitStruct.Pin = GPIO_PIN_0|GPIO_PIN_1;
  GPIO_InitStruct.Mode = GPIO_MODE_ANALOG;
  GPIO_InitStruct.Pull = GPIO_NOPULL;
  HAL_GPIO_Init(GPIOF, &GPIO_InitStruct);

  /*Configure GPIO pin : PC3 */
  GPIO_InitStruct.Pin = GPIO_PIN_3;
  GPIO_InitStruct.Mode = GPIO_MODE_ANALOG;
  GPIO_InitStruct.Pull = GPIO_NOPULL;
  HAL_GPIO_Init(GPIOC, &GPIO_InitStruct);

  /*Configure GPIO pins : PA5 PA6 PA7 PA8
                           PA9 PA10 PA11 PA12 */
  GPIO_InitStruct.Pin = GPIO_PIN_5|GPIO_PIN_6|GPIO_PIN_7|GPIO_PIN_8
                          |GPIO_PIN_9|GPIO_PIN_10|GPIO_PIN_11|GPIO_PIN_12;
  GPIO_InitStruct.Mode = GPIO_MODE_ANALOG;
  GPIO_InitStruct.Pull = GPIO_NOPULL;
  HAL_GPIO_Init(GPIOA, &GPIO_InitStruct);

  /*Configure GPIO pins : PB0 PB1 PB2 PB10
                           PB11 PB12 PB13 PB14
                           PB15 PB5 PB6 PB7
                           PB8 PB9 */
  GPIO_InitStruct.Pin = GPIO_PIN_0|GPIO_PIN_1|GPIO_PIN_2|GPIO_PIN_10
                          |GPIO_PIN_11|GPIO_PIN_12|GPIO_PIN_13|GPIO_PIN_14
                          |GPIO_PIN_15|GPIO_PIN_5|GPIO_PIN_6|GPIO_PIN_7
                          |GPIO_PIN_8|GPIO_PIN_9;
  GPIO_InitStruct.Mode = GPIO_MODE_ANALOG;
  GPIO_InitStruct.Pull = GPIO_NOPULL;
  HAL_GPIO_Init(GPIOB, &GPIO_InitStruct);

  /*Configure GPIO pin : PD2 */
  GPIO_InitStruct.Pin = GPIO_PIN_2;
  GPIO_InitStruct.Mode = GPIO_MODE_ANALOG;
  GPIO_InitStruct.Pull = GPIO_NOPULL;
  HAL_GPIO_Init(GPIOD, &GPIO_InitStruct);

}

/* USER CODE BEGIN 2 */

/* USER CODE END 2 */

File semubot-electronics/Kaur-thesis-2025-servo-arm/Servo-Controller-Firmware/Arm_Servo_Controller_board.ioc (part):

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Mcu.Name=STM32F303R(D-E)Tx
Mcu.Package=LQFP64
Mcu.UserName=STM32F303RDTx
PA0.Mode=IN1-Single-Ended
PA0.Signal=ADC1_IN1
PA1.Mode=IN2-Single-Ended
PA1.Signal=ADC1_IN2
PA13.Mode=JTAG_5_pins
PA13.Signal=SYS_JTMS-SWDIO
PA14.Mode=JTAG_5_pins
PA14.Signal=SYS_JTCK-SWCLK
PA15.Mode=JTAG_5_pins
PA15.Signal=SYS_JTDI
PA2.Mode=IN3-Single-Ended
PA2.Signal=ADC1_IN3
PA3.Mode=IN4-Single-Ended
PA3.Signal=ADC1_IN4
PA4.Mode=IN1-Single-Ended
PA4.Signal=ADC2_IN1
PB3.Mode=JTAG_5_pins
PB3.Signal=SYS_JTDO-TRACESWO
PB4.Mode=JTAG_5_pins
PB4.Signal=SYS_NJTRST
PC0.Signal=S_TIM1_CH1
PC1.Signal=S_TIM1_CH2
PC10.Signal=GPIO_Output
PC11.Signal=GPIO_Output
PC12.Signal=GPIO_Output
PC13.Signal=GPIO_Output
PC14-OSC32_IN.Signal=GPIO_Output
PC15-OSC32_OUT.Signal=GPIO_Output
PC2.Signal=S_TIM1_CH3
PC4.Mode=Asynchronous
PC4.Signal=USART1_TX
PC5.Mode=Asynchronous
PC5.Signal=USART1_RX
PC6.Signal=S_TIM8_CH1
PC7.Signal=S_TIM8_CH2
PC8.Signal=GPIO_Output
PC9.Signal=GPIO_Output
RCC.HSE_VALUE=8000000
RCC.SYSCLKFreq_VALUE=72000000
RCC.SYSCLKSourceVirtual=RCC_SYSCLKSOURCE_PLLCLK
board=custom

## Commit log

2026-04-22 Add SemuBot ROS2 stack manifest
2026-04-23 adding
2026-04-26 semubot_description
2026-05-10 updating files
2026-05-10 Import SemuBot ROS 2 stack into thesis workspace
